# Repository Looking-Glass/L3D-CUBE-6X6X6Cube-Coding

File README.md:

# HOW TO PROGRAM THE 6X6X6 CUBE WITH ARDUINO

Step 1.     Followed the instructions in the Arduino_STM wiki: https://github.com/rogerclarkmelbourne/Arduino_STM32/wiki/Installation

Step 2. 	  Unzip <L3D_CubePixel.zip> and <beta-cube-library.zip> and put these two libraries under arduino library folder  ..\..\arduino-1.6.5-r5-windows\arduino-1.6.5-r5\libraries

Step 3.        Restart Arduino IDE, then select Maple (Rev3) for programming.
**If you can not find Maple(Rev3) on the board menu, replace the Arduino_STM32 folder with this one https://github.com/rogerclarkmelbourne/Arduino_STM32

**Enclosed two Demos x6CubeDemo.zip and x6CubeMusicPack.zip for reference, enjoy!

The Schematic and PCB source files can be open with Eagle PCB.

Enclosed some screenshot for Arauino IDE setting up for reference as well

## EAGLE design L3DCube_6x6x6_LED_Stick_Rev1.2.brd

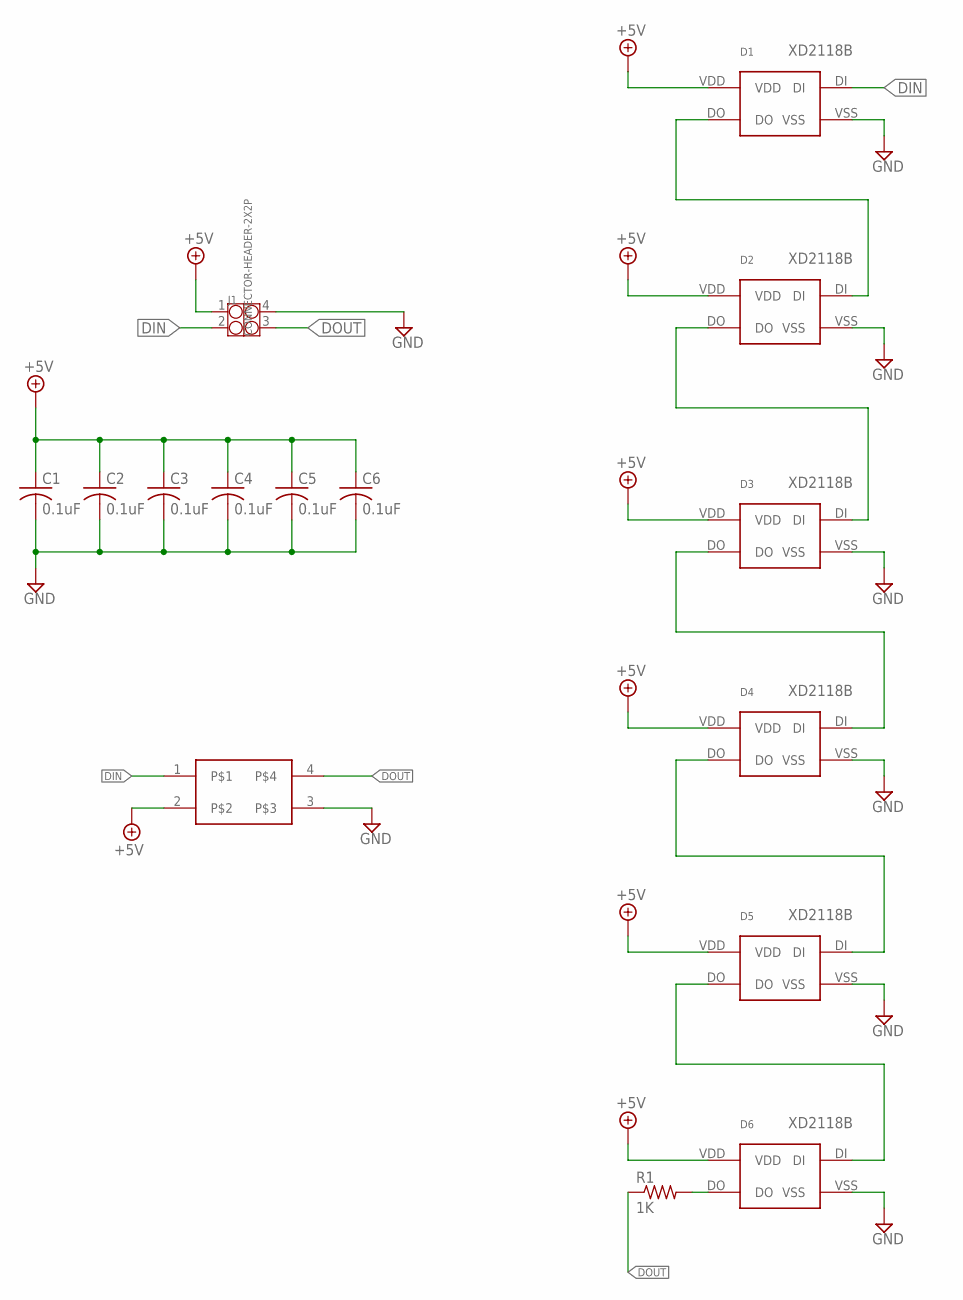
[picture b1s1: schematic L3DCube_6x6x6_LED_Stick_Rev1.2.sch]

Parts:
C1, C2, C3, C4, C5, C6: 0.1uF; C0402
D1, D2, D3, D4, D5, D6: XD2118B; WS2812B
J1: CONNECTOR-HEADER-2X2P; 2X2P-2.54
R1: 1K; R0402
U$1: TESTPAD-2X2-2.54; 2X2P-2.54-TESTPAD

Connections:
+5V: C1.1, C2.1, C3.1, C4.1, C5.1, C6.1, D1.VDD, D2.VDD, D3.VDD, D4.VDD, D5.VDD, D6.VDD, J1.1, U$1.2
DIN: D1.DI, J1.2, U$1.1
DOUT: J1.3, R1.1, U$1.4
GND: C1.2, C2.2, C3.2, C4.2, C5.2, C6.2, D1.VSS, D2.VSS, D3.VSS, D4.VSS, D5.VSS, D6.VSS, J1.4, U$1.3
unnamed: D1.DO, D2.DI
unnamed: D2.DO, D3.DI
unnamed: D3.DO, D4.DI
unnamed: D4.DO, D5.DI
unnamed: D5.DO, D6.DI
unnamed: D6.DO, R1.2

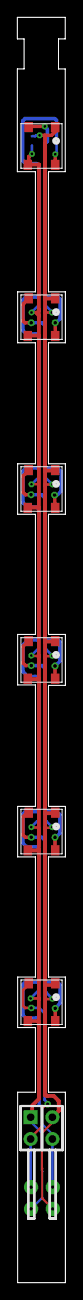
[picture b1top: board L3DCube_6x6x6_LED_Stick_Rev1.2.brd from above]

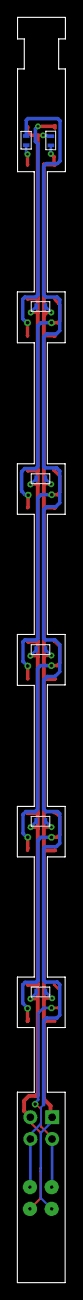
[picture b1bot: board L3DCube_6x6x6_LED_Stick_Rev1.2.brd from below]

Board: 2 copper layers, 5.6 x 147.6 mm, 15 parts (7 on the bottom side), 10 nets.

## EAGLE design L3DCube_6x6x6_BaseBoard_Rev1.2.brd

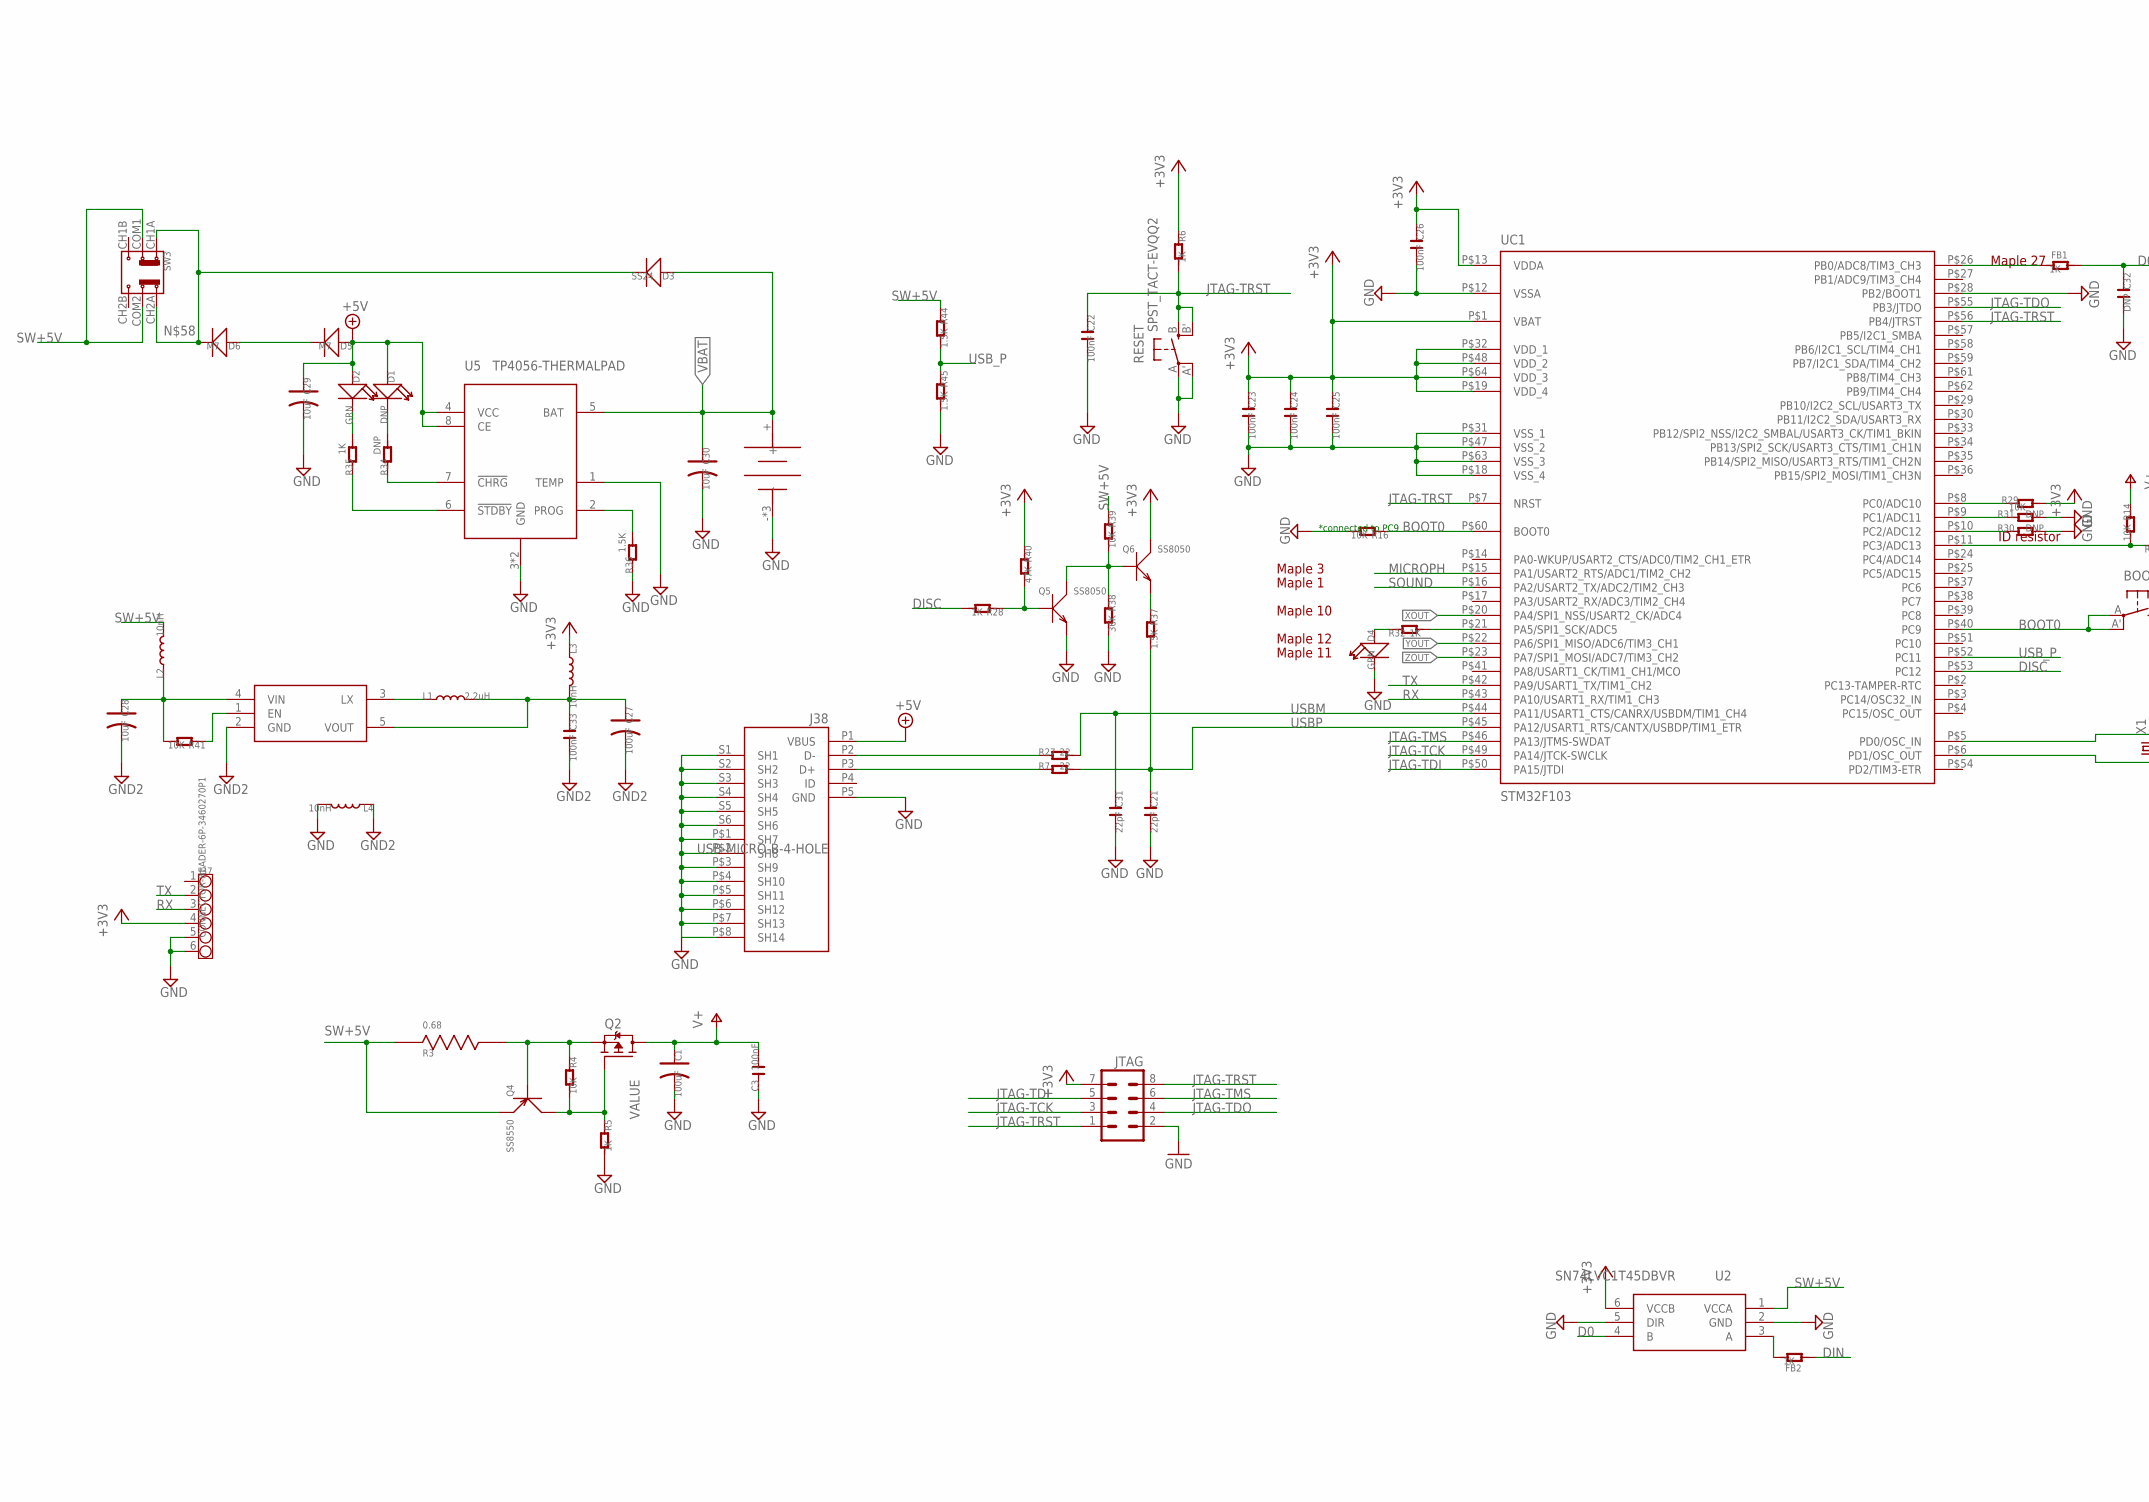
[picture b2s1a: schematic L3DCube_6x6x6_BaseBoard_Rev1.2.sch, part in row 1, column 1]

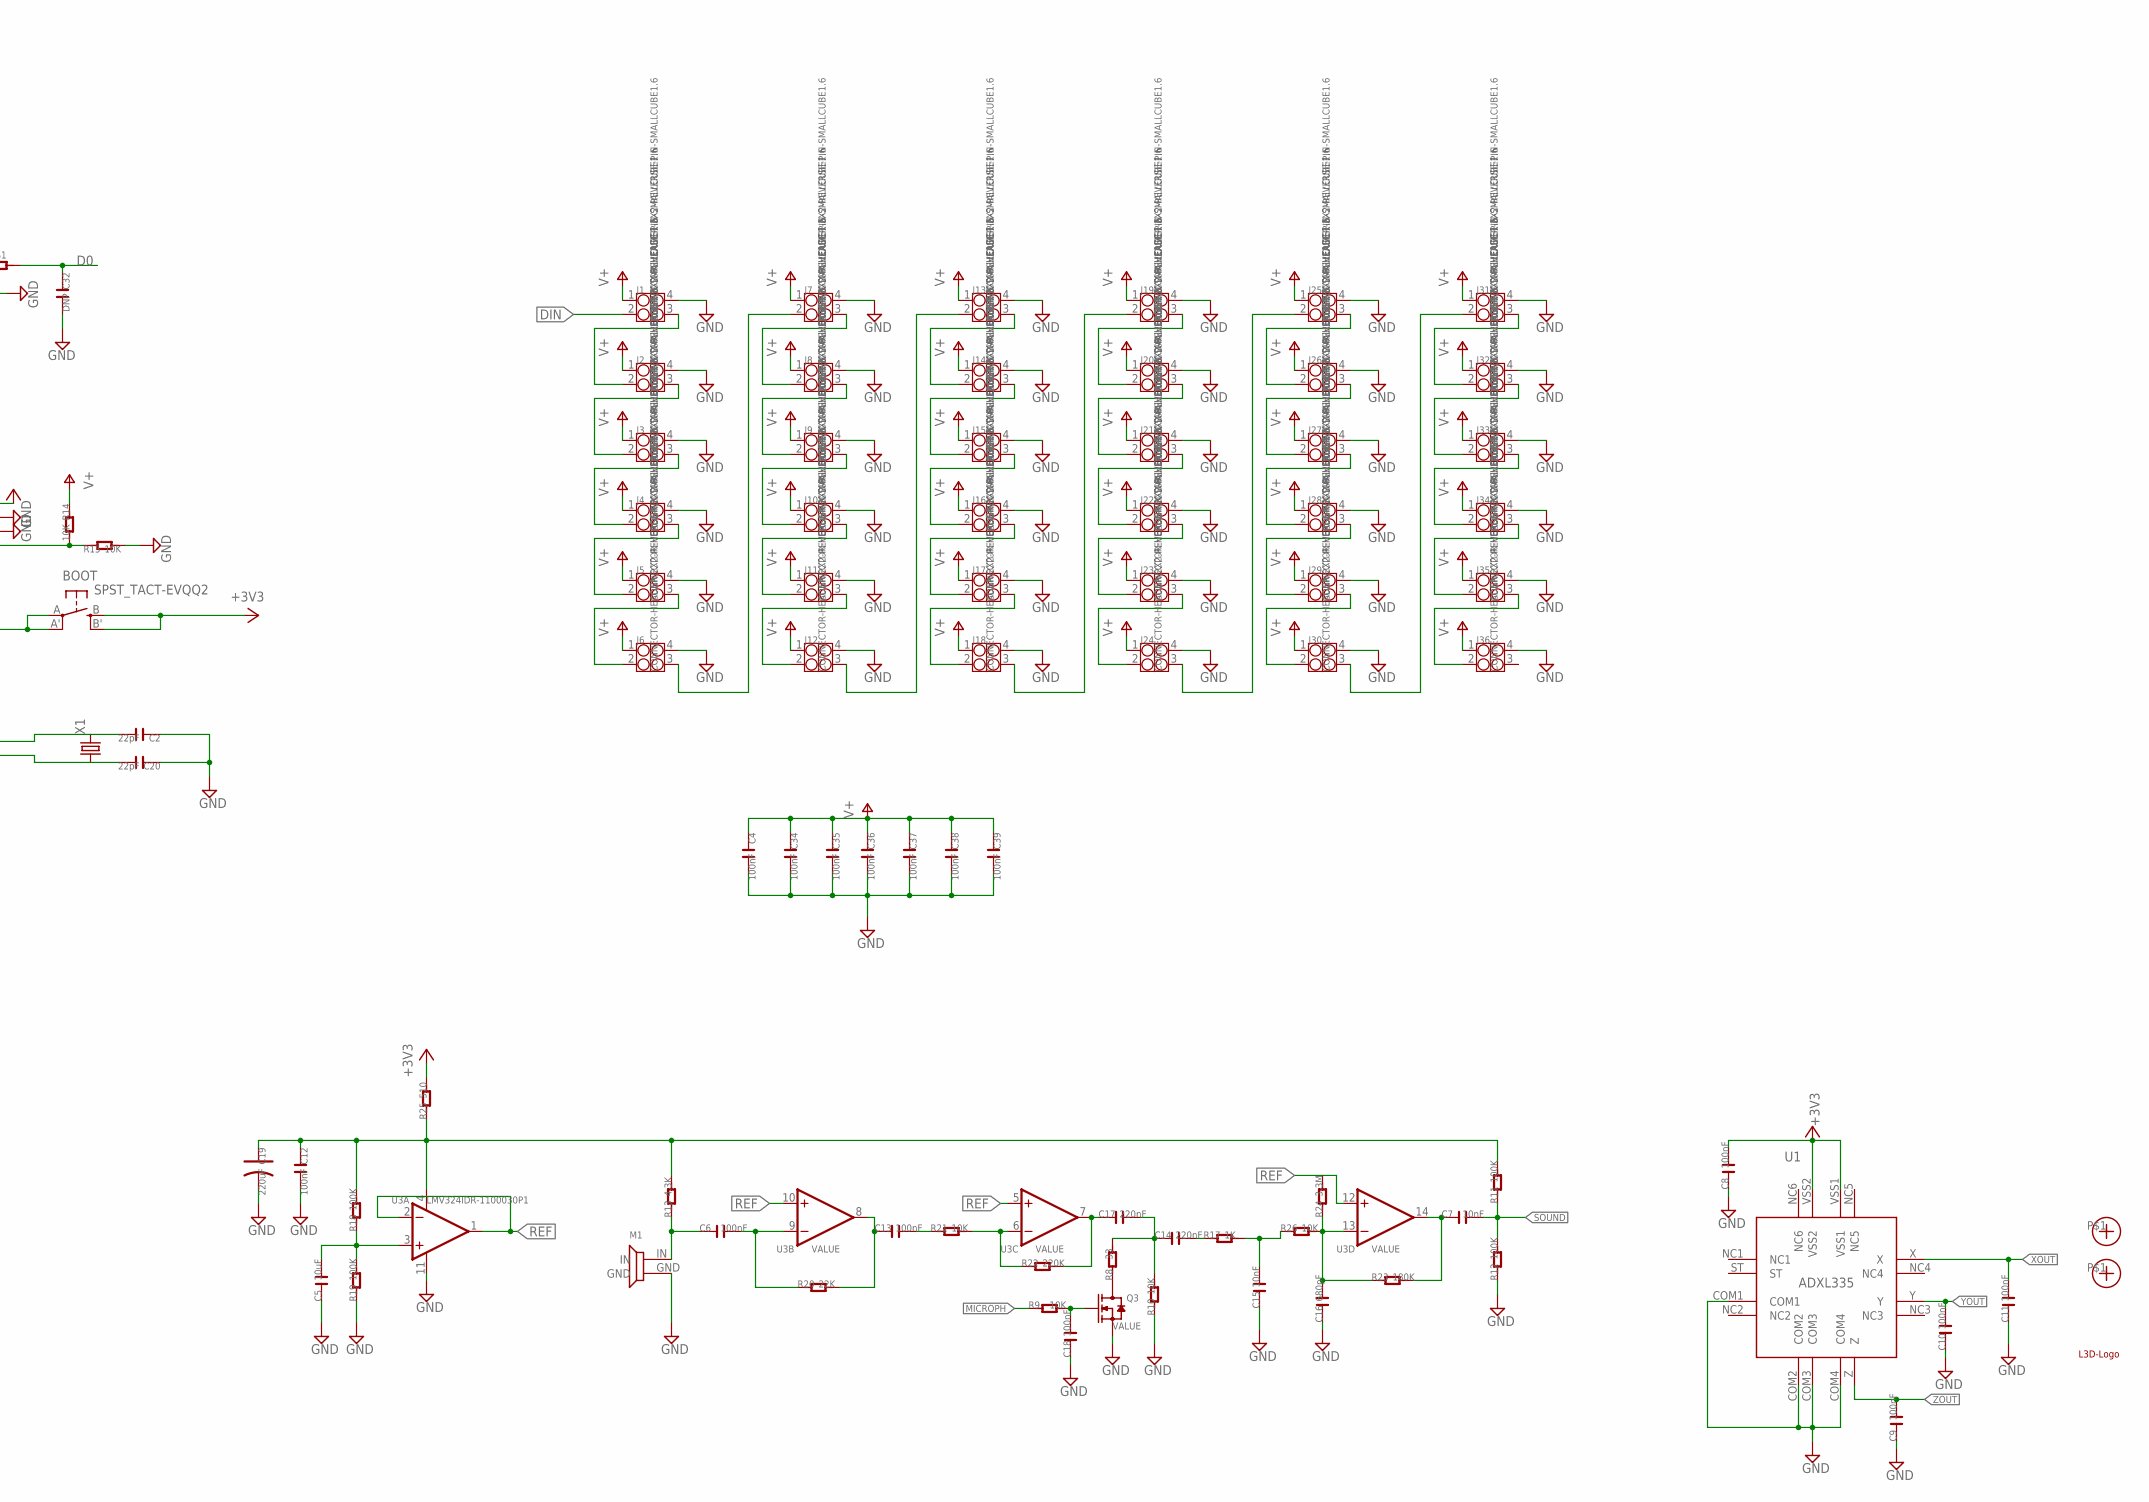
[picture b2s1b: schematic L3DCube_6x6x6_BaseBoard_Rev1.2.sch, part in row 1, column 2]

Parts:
B1: BATTERY; 2P-SMD-2.0-90D
BOOT: SPST_TACT-EVQQ2; EVQ-Q2
C1, C27: 100uF; AVX-B
C2, C20, C21, C31: 22pF; C0603
C3, C4, C6, C8, C9, C10, C11, C12, C13, C18, C22, C23, C24, C25, C26, C33, C34, C35, C36, C37, C38, C39: 100nF; C0603
C5: 10uF; C0603
C7, C15: 10nF; C0603
C14, C17: 220nF; C0603
C16: 680pF; C0603
C19: 220uF; AVX-B
C28, C29, C30: 10uF; AVX-A
C32: DNP; C0603
D1: DNP; LED0603
D2, D4: GRN; LED0603
D3: SS24; SMB
D5, D6: M7; DO-214AC
FB1, FB2: 1K; R0603
J1, J2, J3, J4, J5, J6, J7, J8, J9, J10, J11, J12, J13, J14, J15, J16, J17, J18, J19, J20, J21, J22, J23, J24, J25, J26, J27, J28, J29, J30, J31, J32, J33, J34, J35, J36: CONNECTOR-HEADER-2X2-REVERSE-PIN-SMALLCUBE1.6; 2X2P-2.54-6X6X6-CUBE-TH
J37: CONNECTOR-HEADER-6P-3460270P1; 1X6P-2.54-8.5-BLACK-FEMALE
J38: USB-MICRO-B-4-HOLE; CON2_USB_MICRO_B_AT
JTAG: MA04-2
L1: 2.2uH; L0420
L2, L3, L4: 10nH; L0603
M1: MICROPHONE
Q2: FDD6637; TO252
Q3: 2N7002; SOT23
Q4: SS8550; SOT23
Q5, Q6: SS8050; SOT23
R3: 0.68; RESISTOR-3W-20MM
R4, R9, R10, R14, R15, R16, R21, R26, R29, R39: 10K; R0603
R5, R6, R17, R28, R32, R35: 1K; R0603
R7, R27: 22; R0603
R8: 33; R0603
R11, R12, R18, R19: 100K; R0603
R13: 4.3K; R0603
R20: 22K; R0603
R22: 220K; R0603
R23: 180K; R0603
R24: 3.3M; R0603
R25: 510; R0603
R30, R31, R34: DNP; R0603
R36, R37, R44, R45: 1.5K; R0603
R38: 36K; R0603
R40: 47K; R0603
R41: 10K; R0402
RESET: SPST_TACT-EVQQ2; EVQ-Q2
SW3: SWITCH-22D02
U1: ADXL335
U2: SN74LVC1T45DBVR; SOT23-6
U3: LMV324IDR-1100030P1; SOIC14
U5: TP4056-THERMALPAD; SOIC8-PAD
U11: R8008-33; SOT23-5
U$1: L3D-LOGOL3DCUBE-LOGO-0.8X2.5; L3DCUBE-LOGO-0.8X2.5
U$2, U$3: FIDUCIAL-MARK
UC1: STM32F103; TQFP-10X10-64
X1: CRYSTALSM49; SM49

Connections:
+3V3: BOOT.B (S), BOOT.B' (S1), C8.2, C23.1, C24.1, C25.1, C26.1, J37.4, JTAG.7, L3.1, Q6.3 (C), R6.1, R25.2, R29.1, R40.1, U1.VSS1, U1.VSS2, U2.6 (VCCB), UC1.P$1 (VBAT), UC1.P$13 (VDDA), UC1.P$19 (VDD_4), UC1.P$32 (VDD_1), UC1.P$48 (VDD_2), UC1.P$64 (VDD_3)
+5V: C29.+ (1), D1.+, D2.+, D5.1 (+), J38.P1 (VBUS), U5.4 (VCC), U5.8 (CE)
BOOT0: BOOT.A, BOOT.A' (P1), R16.1, UC1.P$40 (PC9), UC1.P$60 (BOOT0)
D0: C32.1, FB1.1, U2.4 (B)
DIN: FB2.1, J1.2
DISC: R28.2, UC1.P$53 (PC12)
ENABLE: R41.1, U11.1 (EN)
GND: B1.3 (-), B1.4 (-), B1.-, C1.- (2), C2.1, C3.1, C4.2, C5.1, C8.1, C9.1, C10.1, C11.1, C12.2, C15.1, C16.1, C18.1, C19.- (2), C20.1, C21.2, C22.2, C23.2, C24.2, C25.2, C26.2, C29.- (2), C30.- (2), C31.2, C32.2, C34.2, C35.2, C36.2, C37.2, C38.2, C39.2, D4.-, J1.4, J2.4, J3.4, J4.4, J5.4, J6.4, J7.4, J8.4, J9.4, J10.4, J11.4, J12.4, J13.4, J14.4, J15.4, J16.4, J17.4, J18.4, J19.4, J20.4, J21.4, J22.4, J23.4, J24.4, J25.4, J26.4, J27.4, J28.4, J29.4, J30.4, J31.4, J32.4, J33.4, J34.4, J35.4, J36.4, J37.5, J37.6, J38.P5 (GND), J38.P$1 (SH7), J38.P$2 (SH8), J38.P$3 (SH9), J38.P$4 (SH10), J38.P$5 (SH11), J38.P$6 (SH12), J38.P$7 (SH13), J38.P$8 (SH14), J38.S1 (SH1), J38.S2 (SH2), J38.S3 (SH3), J38.S4 (SH4), J38.S5 (SH5), J38.S6 (SH6), JTAG.2, L4.2, M1.GND, Q3.2 (S), Q5.2 (E), R5.2, R10.1, R12.1, R15.2, R16.2, R19.1, R30.2, R31.2, R36.1, R38.2, R45.2, RESET.A, RESET.A' (P1), U1.COM1, U1.COM2, U1.COM3, U1.COM4, U2.2 (GND), U2.5 (DIR), U3.11 (V-), U5.1 (TEMP), U5.3 (GND), U5.GND1 (GND), UC1.P$12 (VSSA), UC1.P$18 (VSS_4), UC1.P$28 (PB2/BOOT1), UC1.P$31 (VSS_1), UC1.P$47 (VSS_2), UC1.P$63 (VSS_3)
GND2: C27.- (2), C28.- (2), C33.2, L4.1, U11.2 (GND)
JTAG-TCK: JTAG.3, UC1.P$49 (PA14/JTCK-SWCLK)
JTAG-TDI: JTAG.5, UC1.P$50 (PA15/JTDI)
JTAG-TDO: JTAG.4, UC1.P$55 (PB3/JTDO)
JTAG-TMS: JTAG.6, UC1.P$46 (PA13/JTMS-SWDAT)
JTAG-TRST: C22.1, JTAG.1, JTAG.8, R6.2, RESET.B (S), RESET.B' (S1), UC1.P$7 (NRST), UC1.P$56 (PB4/JTRST)
LED1: D4.+, R32.1
MICROPH: R9.1, UC1.P$15 (PA1/USART2_RTS/ADC1/TIM2_CH2)
unnamed: J1.3, J2.2
unnamed: J2.3, J3.2
unnamed: J3.3, J4.2
unnamed: J4.3, J5.2
unnamed: J5.3, J6.2
unnamed: J7.3, J8.2
unnamed: J8.3, J9.2
unnamed: J9.3, J10.2
unnamed: J10.3, J11.2
unnamed: J11.3, J12.2
unnamed: J13.3, J14.2
unnamed: J14.3, J15.2
unnamed: J15.3, J16.2
unnamed: J16.3, J17.2
unnamed: J17.3, J18.2
unnamed: J19.3, J20.2
unnamed: J20.3, J21.2
unnamed: J21.3, J22.2
unnamed: J22.3, J23.2
unnamed: J23.3, J24.2
unnamed: J25.3, J26.2
unnamed: J26.3, J27.2
unnamed: J27.3, J28.2
unnamed: J28.3, J29.2
unnamed: J29.3, J30.2
unnamed: J31.3, J32.2
unnamed: J32.3, J33.2
unnamed: J33.3, J34.2
unnamed: J34.3, J35.2
unnamed: J35.3, J36.2
unnamed: J6.3, J7.2
unnamed: C18.2, Q3.1 (G), R9.2
unnamed: J12.3, J13.2
unnamed: J18.3, J19.2
unnamed: J24.3, J25.2
unnamed: J30.3, J31.2
unnamed: C2.2, UC1.P$5 (PD0/OSC_IN), X1.2
unnamed: C20.2, UC1.P$6 (PD1/OSC_OUT), X1.1
unnamed: R14.2, R15.1, UC1.P$11 (PC3/ADC13)
unnamed: J38.P2 (D-), R27.1
unnamed: L1.1, U11.3 (LX)
unnamed: D1.-, R34.2
unnamed: R32.2, UC1.P$21 (PA5/SPI1_SCK/ADC5)
unnamed: FB1.2, UC1.P$26 (PB0/ADC8/TIM3_CH3)
unnamed: R29.2, UC1.P$8 (PC0/ADC10)
unnamed: D2.-, R35.2
unnamed: R34.1, U5.7 (!CHRG)
unnamed: R35.1, U5.6 (!STDBY)
unnamed: R36.2, U5.2 (PROG)
unnamed: R30.1, UC1.P$10 (PC2/ADC12)
unnamed: Q6.2 (E), R37.1
unnamed: C28.+ (1), L2.1, R41.2, U11.4 (VIN)
unnamed: R31.1, UC1.P$9 (PC1/ADC11)
unnamed: J38.P3 (D+), R7.1
unnamed: C27.+ (1), C33.1, L1.2, L3.2, U11.5 (VOUT)
unnamed: FB2.2, U2.3 (A)
unnamed: D3.-, D6.2 (-), SW3.CH1A, SW3.CH2A
unnamed: D5.2 (-), D6.1 (+)
unnamed: Q2.2 (S), Q4.1 (B), R3.2, R4.1
unnamed: Q3.3 (D), R8.1
unnamed: Q2.1 (G), Q4.3 (C), R4.2, R5.1
unnamed: C14.2, R17.1
unnamed: C15.2, R17.2, R26.1
unnamed: C16.2, R23.1, R24.1, R26.2, U3.13 (IN-)
unnamed: Q5.3 (C), Q6.1 (B), R38.1, R39.2
unnamed: C6.1, M1.IN, R13.1
unnamed: Q5.1 (B), R28.1, R40.2
unnamed: C5.2, R18.1, R19.2, U3.3 (IN+)
unnamed: C6.2, R20.1, U3.9 (IN-)
unnamed: C13.1, R20.2, U3.8 (OUT)
unnamed: C13.2, R21.1
unnamed: R21.2, R22.1, U3.6 (IN-)
unnamed: C14.1, C17.2, R8.2, R10.2
unnamed: C12.1, C19.+ (1), R11.2, R13.2, R18.2, R25.1, U3.4 (V+)
unnamed: C7.1, R23.2, U3.14 (OUT)
unnamed: C17.1, R22.2, U3.7 (OUT)
REF: R24.2, U3.1 (OUT), U3.2 (IN-), U3.5 (IN+), U3.10 (IN+), U3.12 (IN+)
RX: J37.3, UC1.P$43 (PA10/USART1_RX/TIM1_CH3)
SOUND: C7.2, R11.1, R12.2, UC1.P$16 (PA2/USART2_TX/ADC2/TIM2_CH3)
SW+5V: L2.2, Q4.2 (E), R3.1, R39.1, R44.1, SW3.COM1, SW3.COM2, U2.1 (VCCA)
TX: J37.2, UC1.P$42 (PA9/USART1_TX/TIM1_CH2)
USBM: C31.1, R27.2, UC1.P$44 (PA11/USART1_CTS/CANRX/USBDM/TIM1_CH4)
USBP: C21.1, R7.2, R37.2, UC1.P$45 (PA12/USART1_RTS/CANTX/USBDP/TIM1_ETR)
USB_P: R44.2, R45.1, UC1.P$52 (PC11)
V+: C1.+ (1), C3.2, C4.1, C34.1, C35.1, C36.1, C37.1, C38.1, C39.1, J1.1, J2.1, J3.1, J4.1, J5.1, J6.1, J7.1, J8.1, J9.1, J10.1, J11.1, J12.1, J13.1, J14.1, J15.1, J16.1, J17.1, J18.1, J19.1, J20.1, J21.1, J22.1, J23.1, J24.1, J25.1, J26.1, J27.1, J28.1, J29.1, J30.1, J31.1, J32.1, J33.1, J34.1, J35.1, J36.1, Q2.3 (D), R14.1
VBAT: B1.+, C30.+ (1), D3.+, U5.5 (BAT)
XOUT: C11.2, U1.X, UC1.P$20 (PA4/SPI1_NSS/USART2_CK/ADC4)
YOUT: C10.2, U1.Y, UC1.P$22 (PA6/SPI1_MISO/ADC6/TIM3_CH1)
ZOUT: C9.2, U1.Z, UC1.P$23 (PA7/SPI1_MOSI/ADC7/TIM3_CH2)

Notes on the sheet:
*connected to PC9
ID resistor
Maple 27
Maple 3
Maple 1
Maple 10
Maple 12
Maple 11

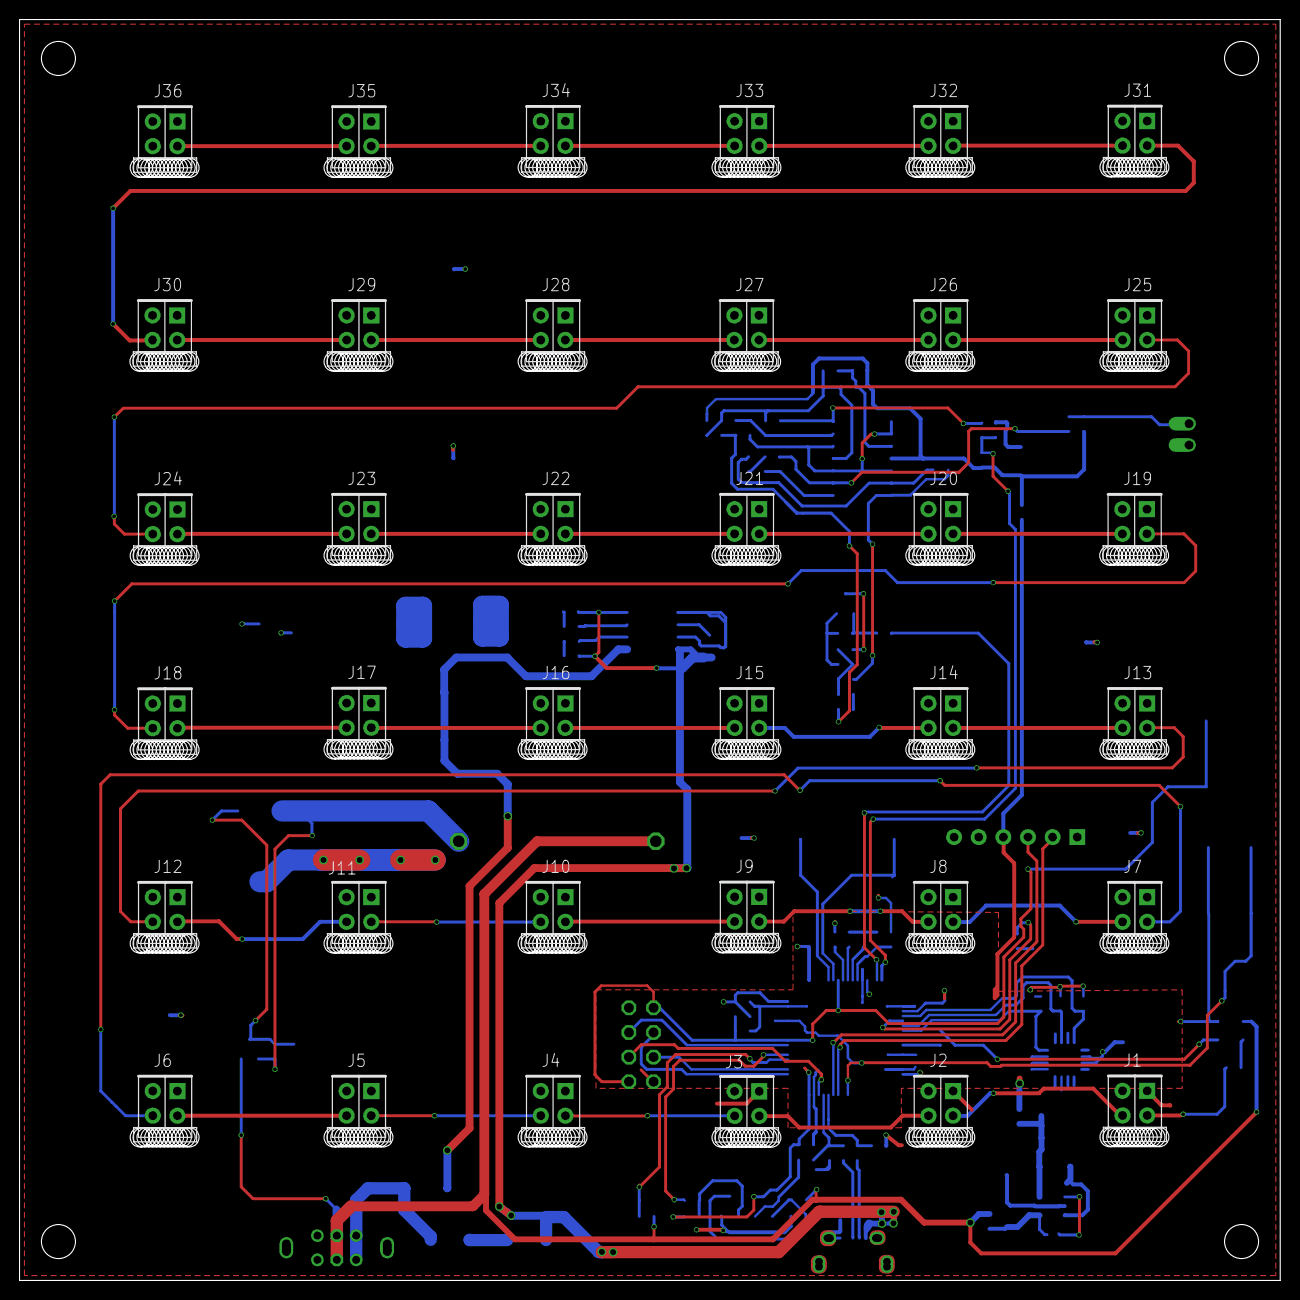
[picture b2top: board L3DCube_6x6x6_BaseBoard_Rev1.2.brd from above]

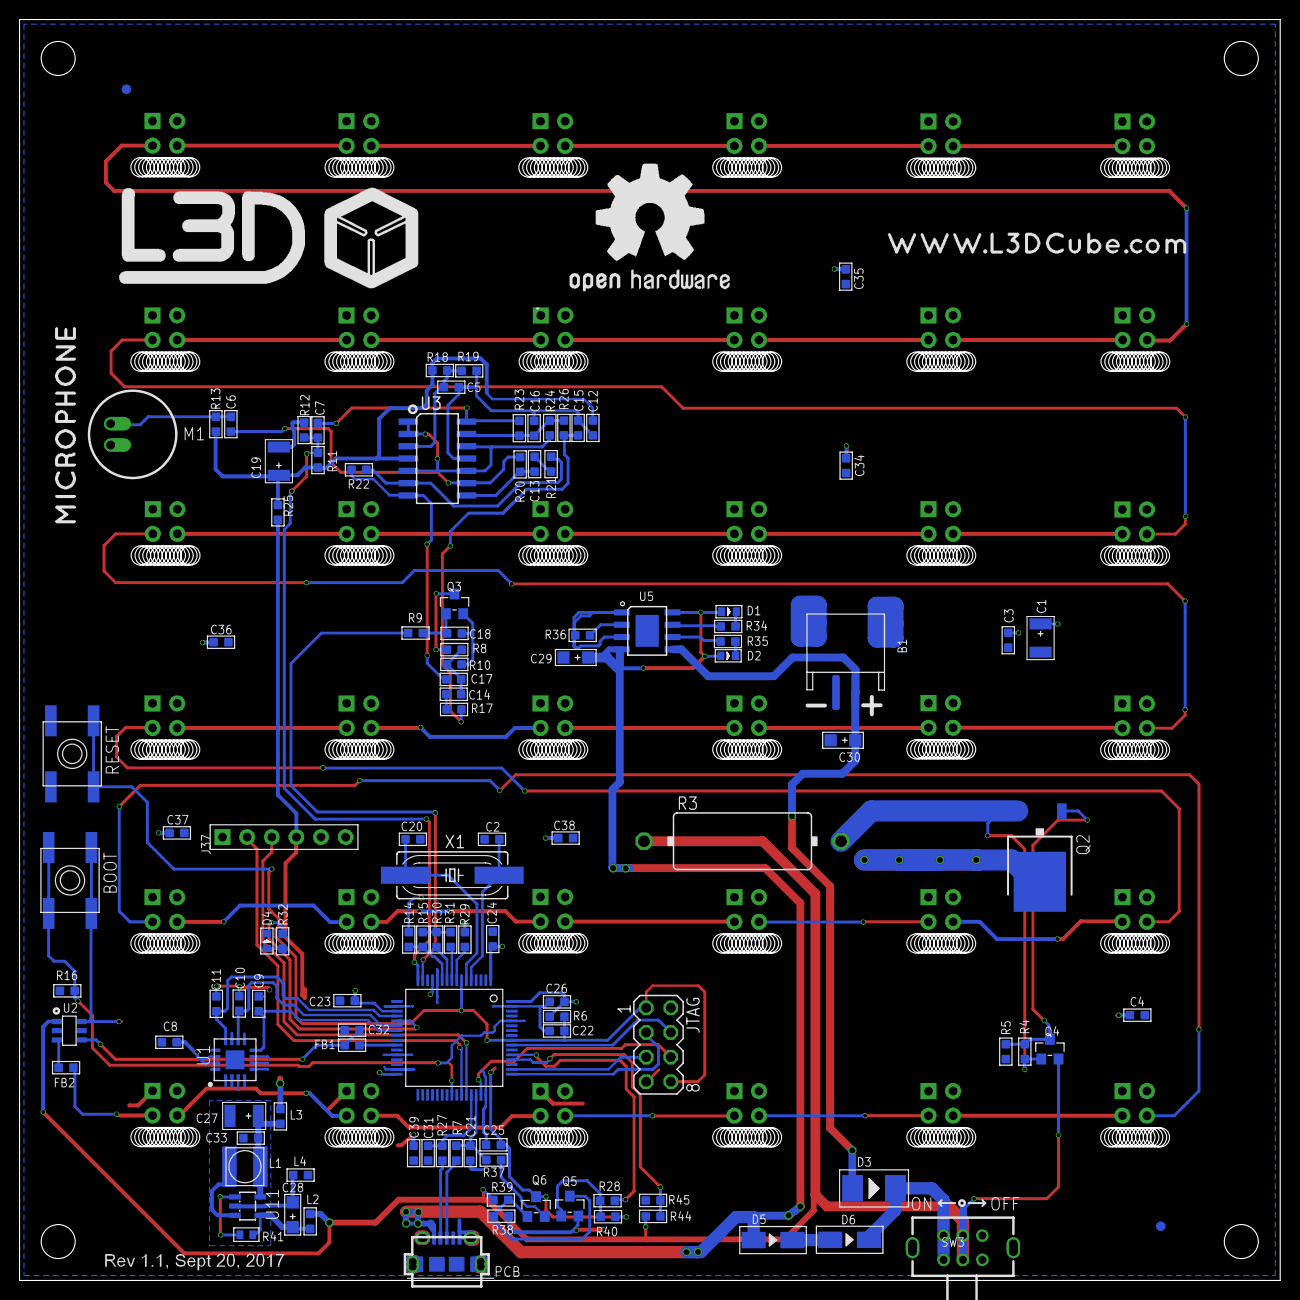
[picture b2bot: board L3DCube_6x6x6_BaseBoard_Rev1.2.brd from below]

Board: 2 copper layers, 130.0 x 130.0 mm, 150 parts (114 on the bottom side), 105 nets.
